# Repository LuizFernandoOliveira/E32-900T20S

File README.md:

# E32-900T20S Shield
 LoRa IoT Module

Electronic circuit designed to communicate between the E32-900T20S module and a microcontrolled/embedded system.

- The J1 connector is designed to fit into a Raspberry Pi.
- The J2 connector was designed to be used on a breadboard.
- The J3 connector was designed to be used with other projects (by the author) that have this type of connector.
- The control signal "LORA_ON" allows turning the module on and off.
- The GND_ON control signal is a signal sent from another board that enables/disables the board's GND. In this case, resistor R1 must be soldered. If you don't need to control the board's GND, just solder resistor R2.

**Front-view:**

**Back-view:**

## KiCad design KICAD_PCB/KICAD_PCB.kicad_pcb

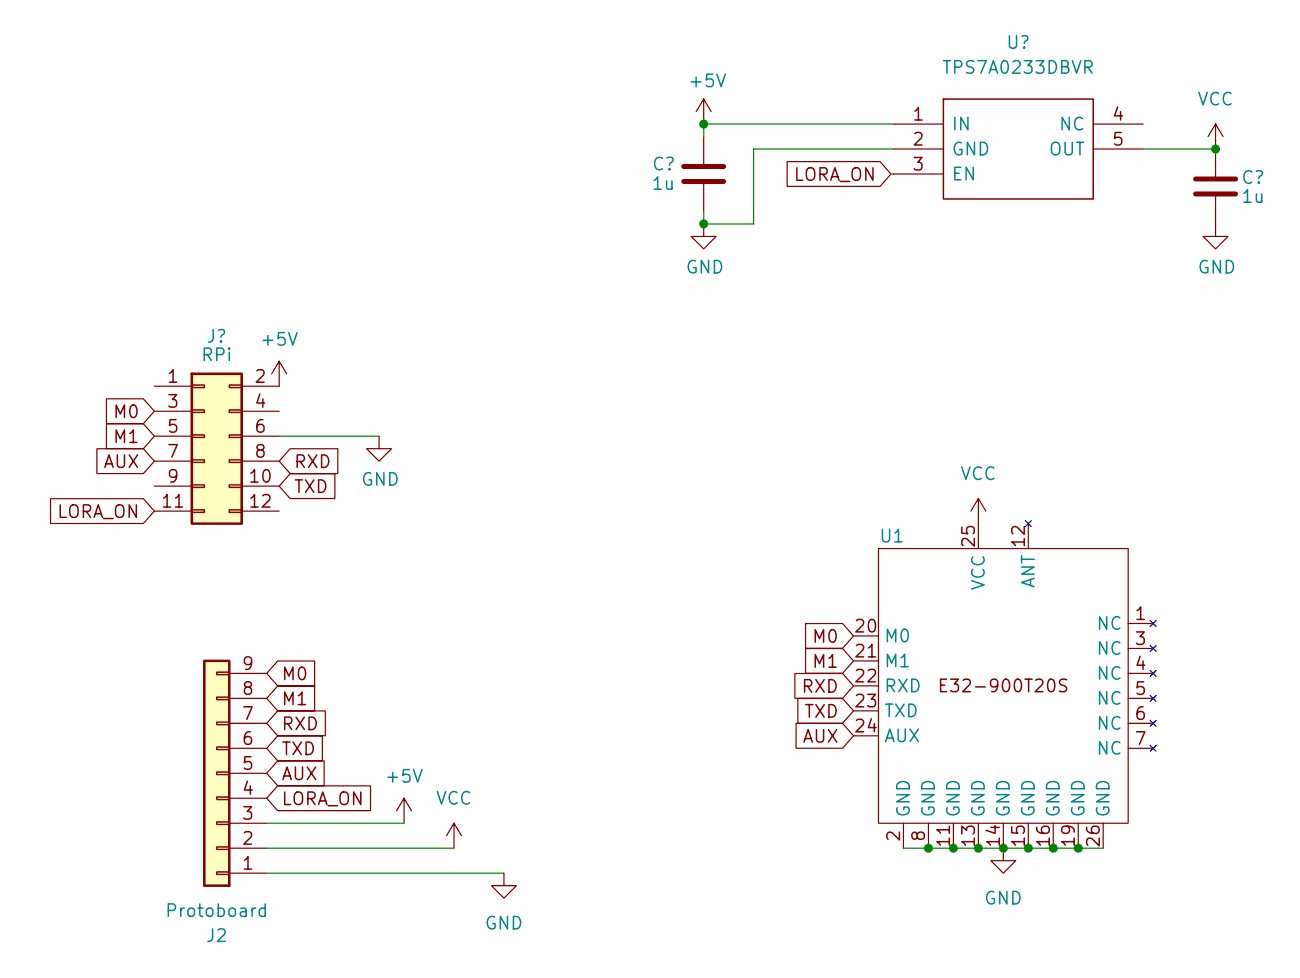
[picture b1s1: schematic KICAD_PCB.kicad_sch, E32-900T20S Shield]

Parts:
C1, C2: 1u; C_0805_2012Metric
J1: RPi; PinSocket_2x06_P2.54mm_Vertical
J2: Protoboard; PinHeader_1x09_P2.54mm_Horizontal
U1: E32-900T20S
U2: TPS7A0233DBVR; SOT95P280X145-5N; Manufacturer_Part_Number TPS7A0233DBVR; Mouser Part Number 595-TPS7A0233DBVR

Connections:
+5V: C1.1, J1.2, J2.3, U2.1 (IN)
AUX: J1.7, J2.5, U1.24 (AUX)
GND: C1.2, C2.2, J1.6, J2.1, U1.2 (GND), U1.8 (GND), U1.11 (GND), U1.13 (GND), U1.14 (GND), U1.15 (GND), U1.16 (GND), U1.19 (GND), U1.26 (GND), U2.2 (GND)
LORA_ON: J1.11, J2.4, U2.3 (EN)
M0: J1.3, J2.9, U1.20 (M0)
M1: J1.5, J2.8, U1.21 (M1)
RXD: J1.8, J2.7, U1.22 (RXD)
TXD: J1.10, J2.6, U1.23 (TXD)
VCC: C2.1, J2.2, U1.25 (VCC), U2.5 (OUT)

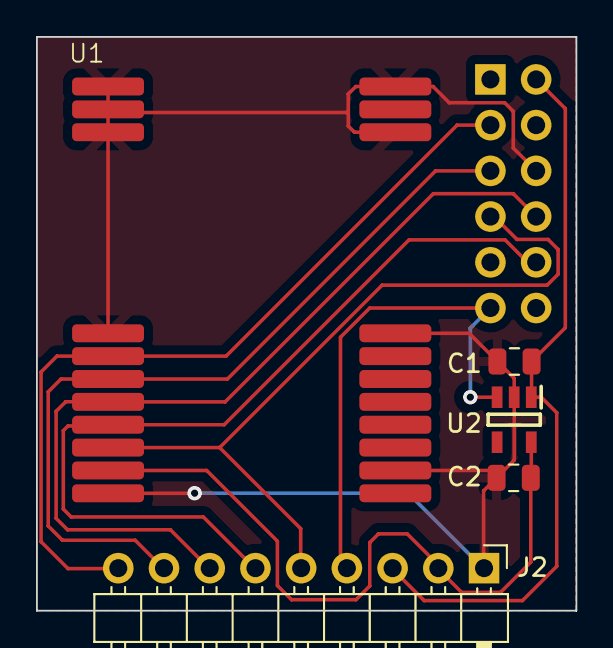
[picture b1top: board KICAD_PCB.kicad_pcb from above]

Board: 2 copper layers, 30.0 x 31.9 mm, 6 parts (1 on the bottom side), 9 nets.

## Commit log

2024-01-27 Initial commint
2024-01-27 Labels ajusts
